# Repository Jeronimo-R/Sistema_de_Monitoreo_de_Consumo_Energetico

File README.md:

# Sistema_de_Monitoreo_Energetico
Repositorio del proyecto "Sistema de Monitoreo Energético" de la clase de Taller de electrónica. Aquí se encontrara la documentación y avances del proyecto

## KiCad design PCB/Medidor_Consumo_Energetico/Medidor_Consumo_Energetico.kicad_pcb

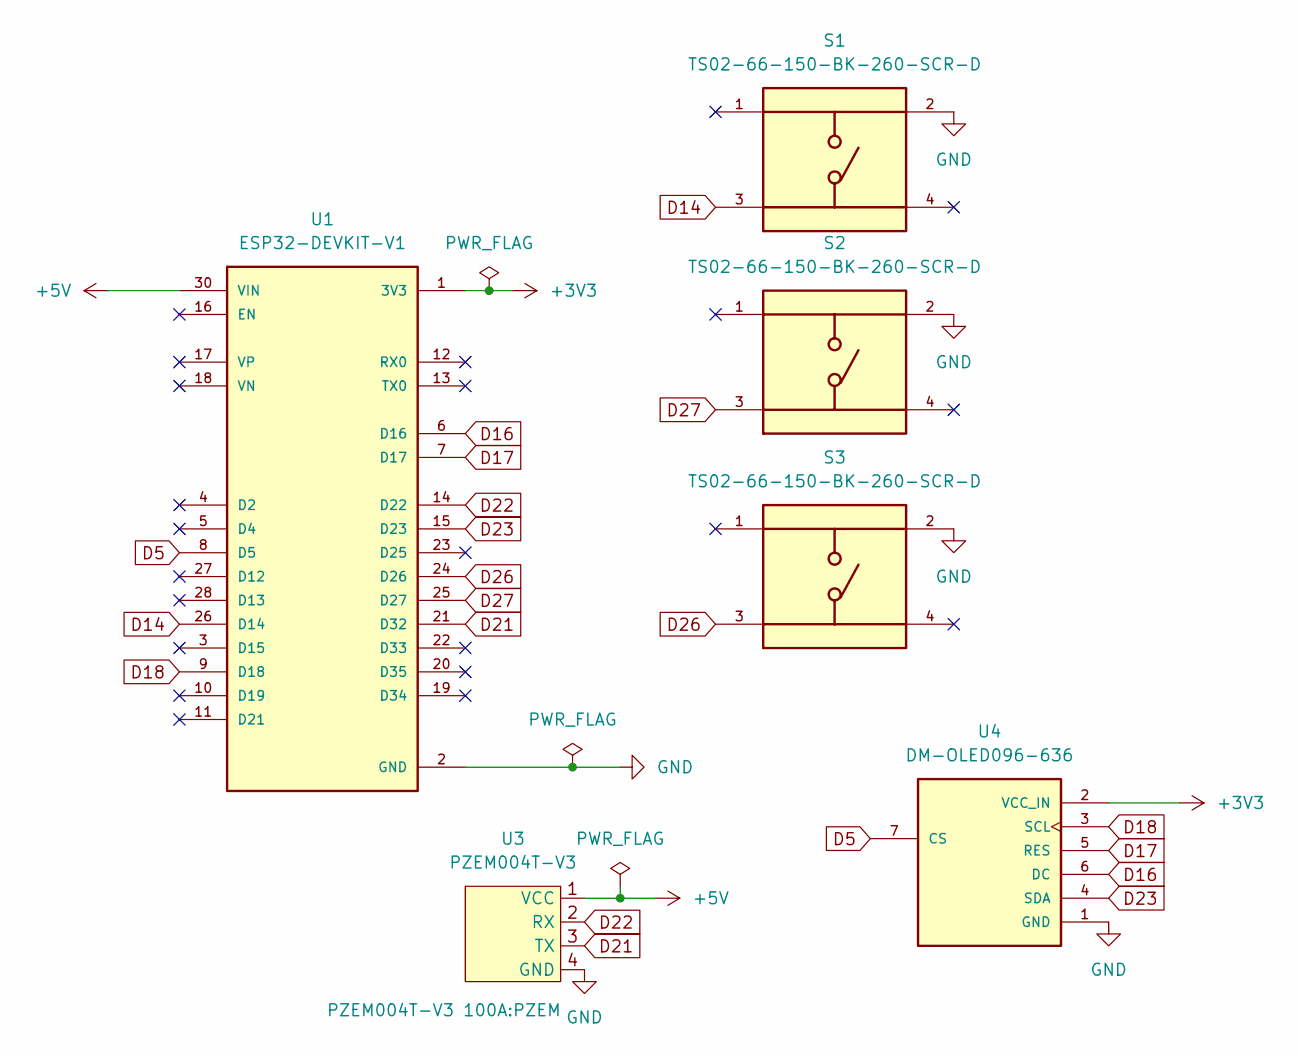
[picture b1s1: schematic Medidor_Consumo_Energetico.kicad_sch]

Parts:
S1, S2, S3: TS02-66-150-BK-260-SCR-D; SW_TS02-66-150-BK-260-SCR-D; PARTREV 1.0
U1: ESP32-DEVKIT-V1; MODULE_ESP32_DEVKIT_V1; PARTREV N/A
U3: PZEM004T-V3; PZEM
U4: DM-OLED096-636; Oled module (only pin); PARTREV 2018-09-10

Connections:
+3V3: U1.1 (3V3), U4.2 (VCC_IN)
+5V: U1.30 (VIN), U3.1 (VCC)
D5: U1.8 (D5), U4.7 (CS)
D14: S1.3, U1.26 (D14)
D16: U1.6 (D16), U4.6 (DC)
D17: U1.7 (D17), U4.5 (RES)
D18: U1.9 (D18), U4.3 (SCL)
D21: U1.21 (D32), U3.3 (TX)
D22: U1.14 (D22), U3.2 (RX)
D23: U1.15 (D23), U4.4 (SDA)
D26: S3.3, U1.24 (D26)
D27: S2.3, U1.25 (D27)
GND: S1.2, S2.2, S3.2, U1.2 (GND), U1.29 (GND), U3.4 (GND), U4.1 (GND)

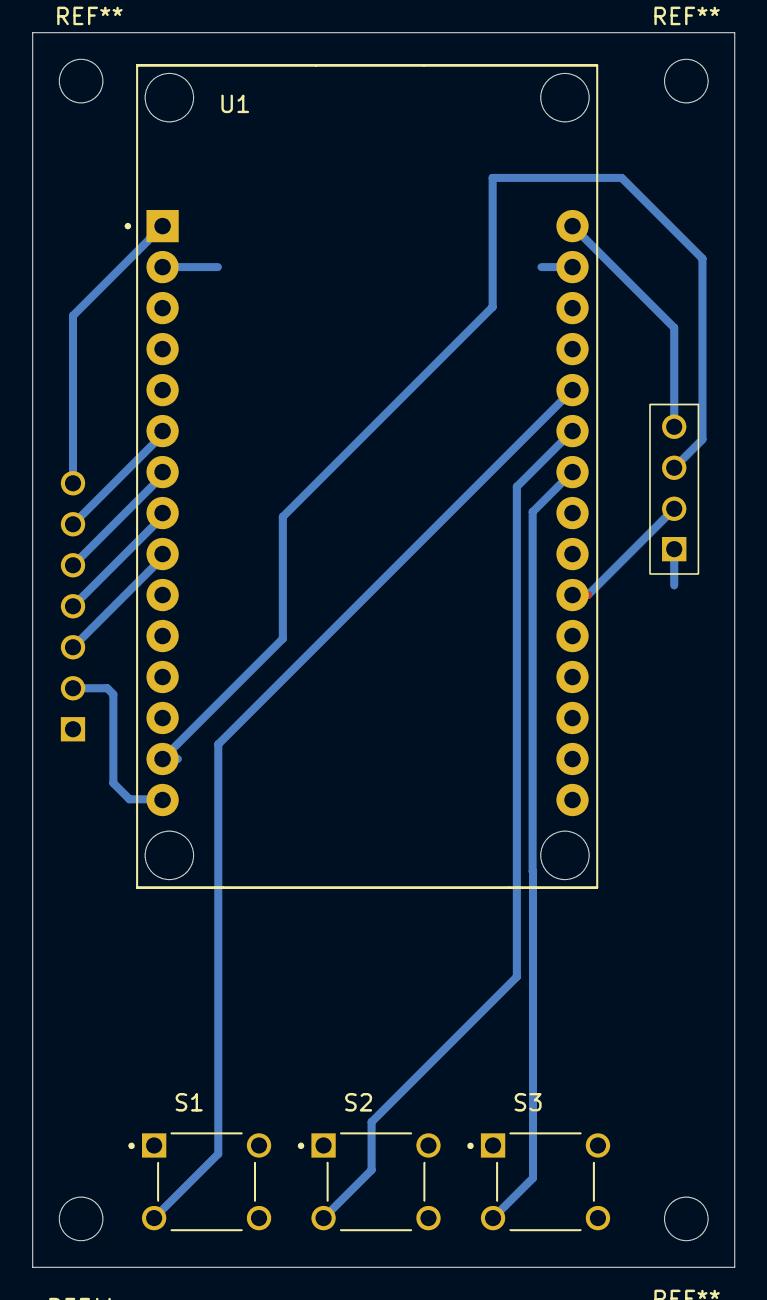
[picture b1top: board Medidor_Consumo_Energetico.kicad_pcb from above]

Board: 2 copper layers, 43.5 x 76.5 mm, 6 parts (0 on the bottom side), 13 nets.

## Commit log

2025-12-09 Refactor project summary in README.md
    Reorganize and clarify the project summary in README.
2025-12-10 Archivos PCB
2025-12-12 Integrate web interface for data display
    Added a graphical interface for better data visualization.
2025-12-12 Update README with details on wall socket box
    Added a description about the wall socket box acquisition and its implementation issues.
